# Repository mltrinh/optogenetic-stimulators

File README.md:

# Optogenetic Stimulators
Martin Trinh Bioengineering 2024 Capstone. This project aimed to create new optogenetic stimulator boxes for the Moritz Lab to control LED spinal cord implants.

# Optogenetic Stimulator Usage
A picture of the finished box is shown below. 

On the left is a front view picture of the box. To control an LED optogenetic implant, insert the LED anode wire into the **upper** red socket and LED cathode wire into the **upper** black socket. The **lower** red and black sockets can be used to plug in thermistor wires if applicable. *Note: The order the thermistor is plugged in does not matter.*

On the right is a top view picture of the box. The OLED monitor displays the voltage that is sent to the LED Driver (correlated with LED Intensity) and temperature if applicable.

# Necessary Materials per Box and Approximate Cost
See table below for necessary materials to construct one optogenetic box. **Ensure that the components bought will fit into the PCB and housing unit. If components do not fit, the files under "PCB Files" and "3D Printing Files" may need to be adjusted accordingly.**

| Name                                          | Quantity | Unit Price | Price per box |
|-----------------------------------------------|:--------:| :---: |:-------------:|
| PCB Board                                     |    1     | $5.33 |     $5.33     |
| Banana Plug                                   |    4     | $1.20 |     $4.80     |
| 500 mA Diode                                  |    1     | $0.36 |     $0.36     |
| 2 A Diode                                     |    1     | $0.45 |     $0.45     |
| N-Channel 60V 30A (Tc) 70W (Tc) TO-220 MOSFET |    1     | $1.45 |     $1.45     |
| 10 uF Capacitor                               |    2     | $0.17 |     $0.34     |
| 0.15 Ohm Resistor 1% Tolerance                |    1     | $0.69 |     $0.69     |
| 100 kOhm Resistor 0.1% Tolerance              |    1     | $0.39 |     $0.39     |
| 1 kOhm Resistor 5% Tolerance                  |    1     | $0.15 |     $0.15     |
| 10 kOhm Potentiometer                         |    1     | $1.61 |     $1.61     |
| AL8860WT-7 LED Driver                         |    1     | $0.68 |     $0.68     |
| 100 uH Inductor                               |    1     | $0.63 |     $0.63     |
| QT PY M0                                      |    1     | $7.50 |     $7.50     |
| JST-PH 2-pin                                  |    2     | $0.75 |     $1.50     |
| 10 Kohm Resistor 1% Tol                       |    1     |$0.10|     $0.10     |
| Hinge                                         |    1     |$3.80|     $3.80     |
| 7 Position Header                             |     2    |$0.62|     $1.24     |
| Push Button Switch DPST                       | 1 |$2.12|     $2.12     |
| PLA                                           | ~80 grams|$0.014/gram|     $1.12     |
| Stemma QT connector                           | 1 | $0.95|     $0.95     |
| OLED Display                                  | 1 | $17.50|    $17.50     |
| Lithium Ion Cylindrical Battery 3.7V 2.2 A    | 2 | $9.95|    $19.90     |
|                                               | | Total Cost |    $72.61     |

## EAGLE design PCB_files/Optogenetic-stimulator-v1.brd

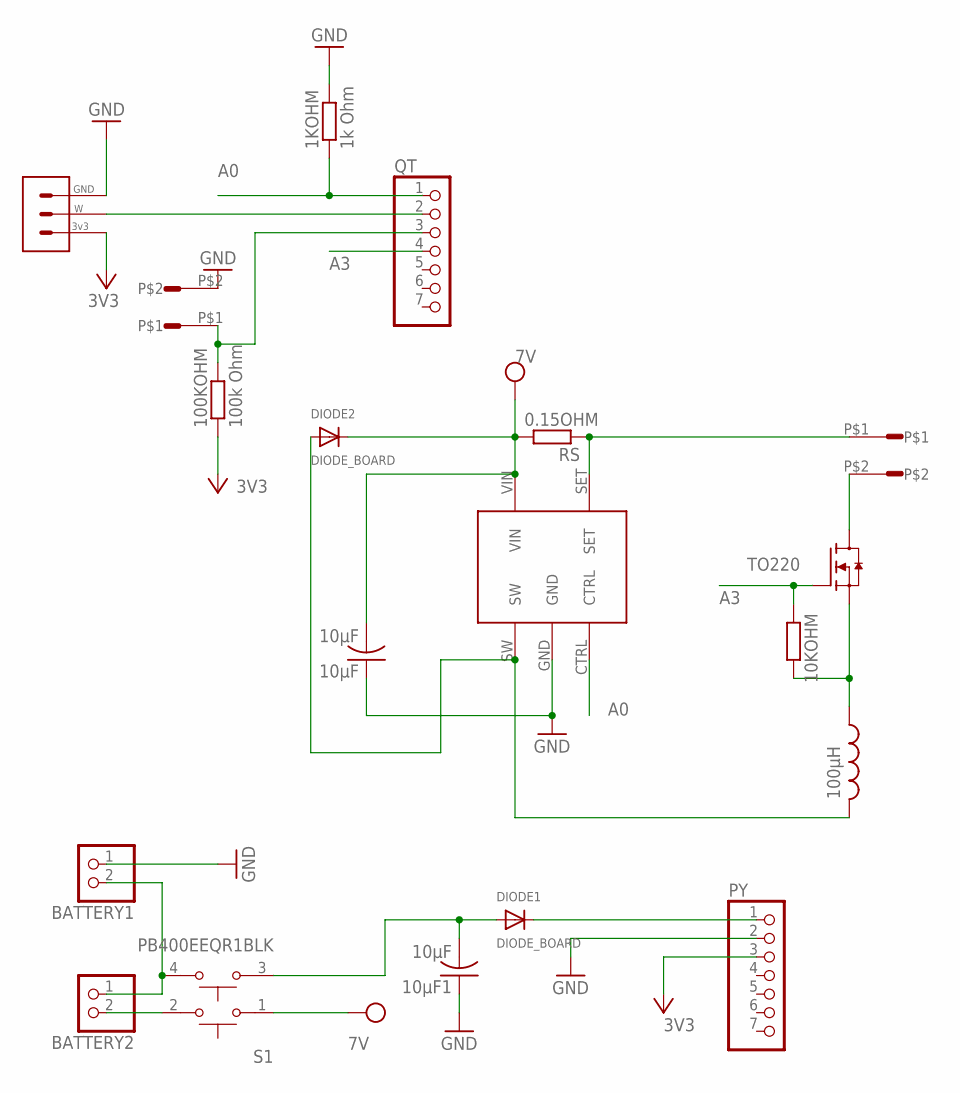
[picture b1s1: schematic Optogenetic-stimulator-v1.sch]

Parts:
1KOHM: 1k Ohm; M1206
10KOHM: R-EU_M1206; M1206
10µF, 10µF1: 10µF; C1206
100KOHM: 100k Ohm; M1206
AL8860WT1: AL8860WT
BATTERY1, BATTERY2: JST_2PIN-THM; JST-PH-2-THM
DIODE1, DIODE2: DIODE_BOARD; DIODE
LED: UNIVERSAL_PAD
NTC: UNIVERSAL_PAD
PY: PINHD-1X7; 1X07
QT: PINHD-1X7; 1X07
RS: 0.15OHM; M1206
S1: PB400EEQR1BLK; SW_PB400EEQR1BLK
TO220: MOSFET-TO220; TO220
U$1: BOARD_INDUCTOR; INDUCTOR
U$6: POTENTIOMETER_BOARD

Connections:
3V3: 100KOHM.1, PY.3, U$6.3V3
7V: 10µF.2, AL8860WT1.VIN, DIODE2.P$2 (C), RS.2, S1.1
A0: 1KOHM.1, AL8860WT1.CTRL, QT.1
A3: 10KOHM.1, QT.4, TO220.1 (G)
GND: 1KOHM.2, 10µF.1, 10µF1.1, AL8860WT1.GND, BATTERY1.1 (2), NTC.P$2, PY.2, U$6.GND
unnamed: BATTERY1.2 (1), BATTERY2.1 (2), S1.4
unnamed: DIODE1.P$2 (C), PY.1
unnamed: LED.P$2, TO220.2 (D)
unnamed: 10µF1.2, DIODE1.P$1 (A), S1.3
unnamed: 100KOHM.2, NTC.P$1, QT.3
unnamed: BATTERY2.2 (1), S1.2
unnamed: AL8860WT1.SW, DIODE2.P$1 (A), U$1.P$2 (2)
unnamed: QT.2, U$6.W
unnamed: AL8860WT1.SET, LED.P$1, RS.1
unnamed: 10KOHM.2, TO220.3 (S), U$1.P$1 (1)

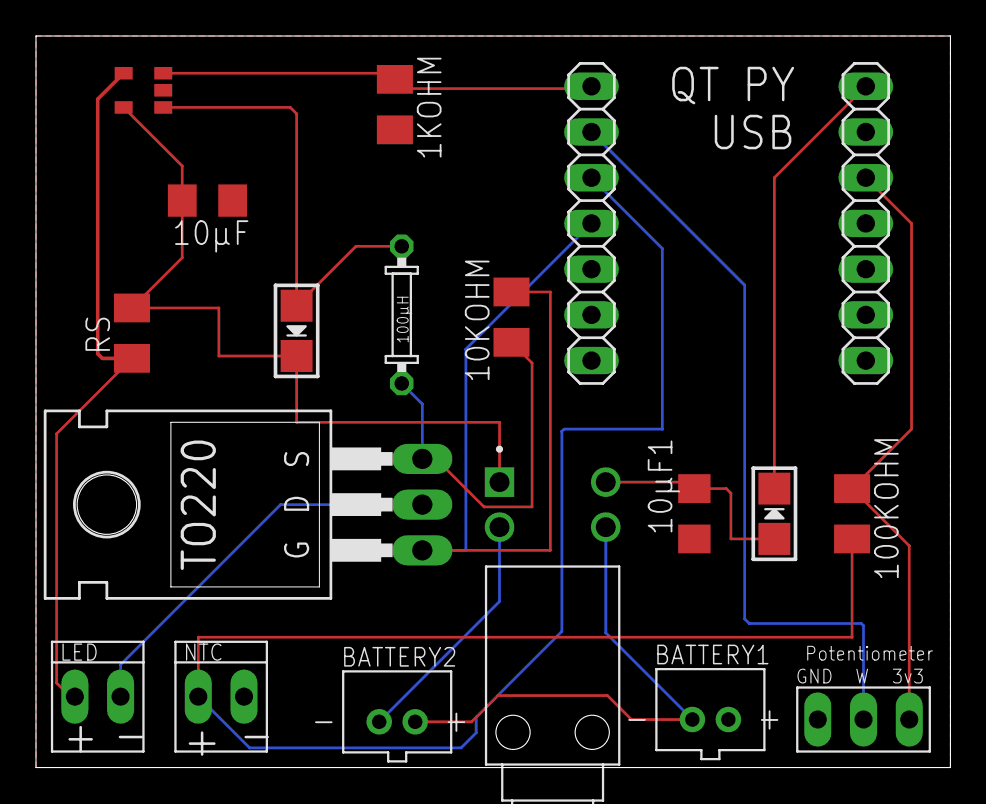
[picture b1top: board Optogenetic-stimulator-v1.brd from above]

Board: 2 copper layers, 50.8 x 40.6 mm, 19 parts (0 on the bottom side), 15 nets.

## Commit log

2024-11-05 Files to print the 3D housing unit for optogenetic stimulators
2024-11-05 Arduino IDE code for the QT PY M0 microcontroller
2024-11-05 Files for creating PCB board of optogenetic stimulators
2024-11-05 Included usage and necessary materials section
